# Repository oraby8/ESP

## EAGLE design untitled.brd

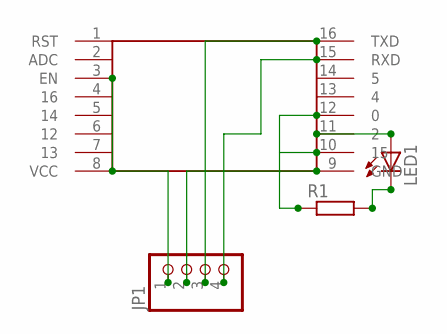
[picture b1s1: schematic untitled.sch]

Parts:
JP1: PINHD-1X4; 1X04
LED1: LED3MM
R1: R-EU_0204/2V; 0204V
U$1: ESP8266-12E; ESP

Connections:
unnamed: LED1.K (C), R1.2
unnamed: LED1.A, U$1.11 (2)
unnamed: JP1.2, R1.1, U$1.9 (GND), U$1.10 (15), U$1.12 (0)
unnamed: JP1.4, U$1.15 (RXD)
unnamed: JP1.3, U$1.16 (TXD)
unnamed: JP1.1, U$1.3 (EN), U$1.8 (VCC)

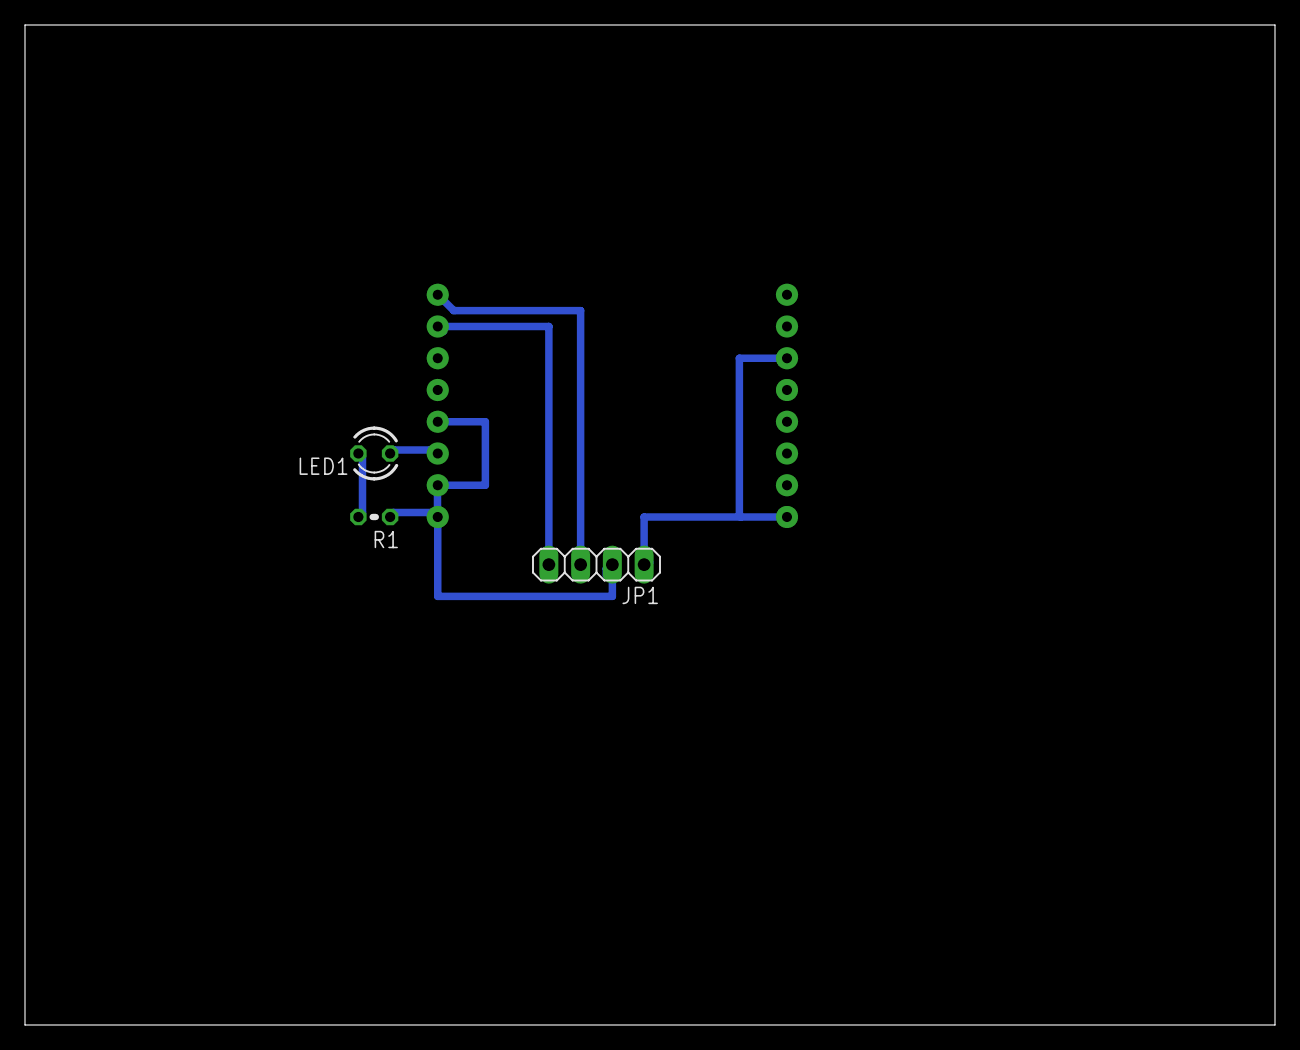
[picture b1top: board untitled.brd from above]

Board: 2 copper layers, 100.0 x 80.0 mm, 4 parts (1 on the bottom side), 6 nets.
